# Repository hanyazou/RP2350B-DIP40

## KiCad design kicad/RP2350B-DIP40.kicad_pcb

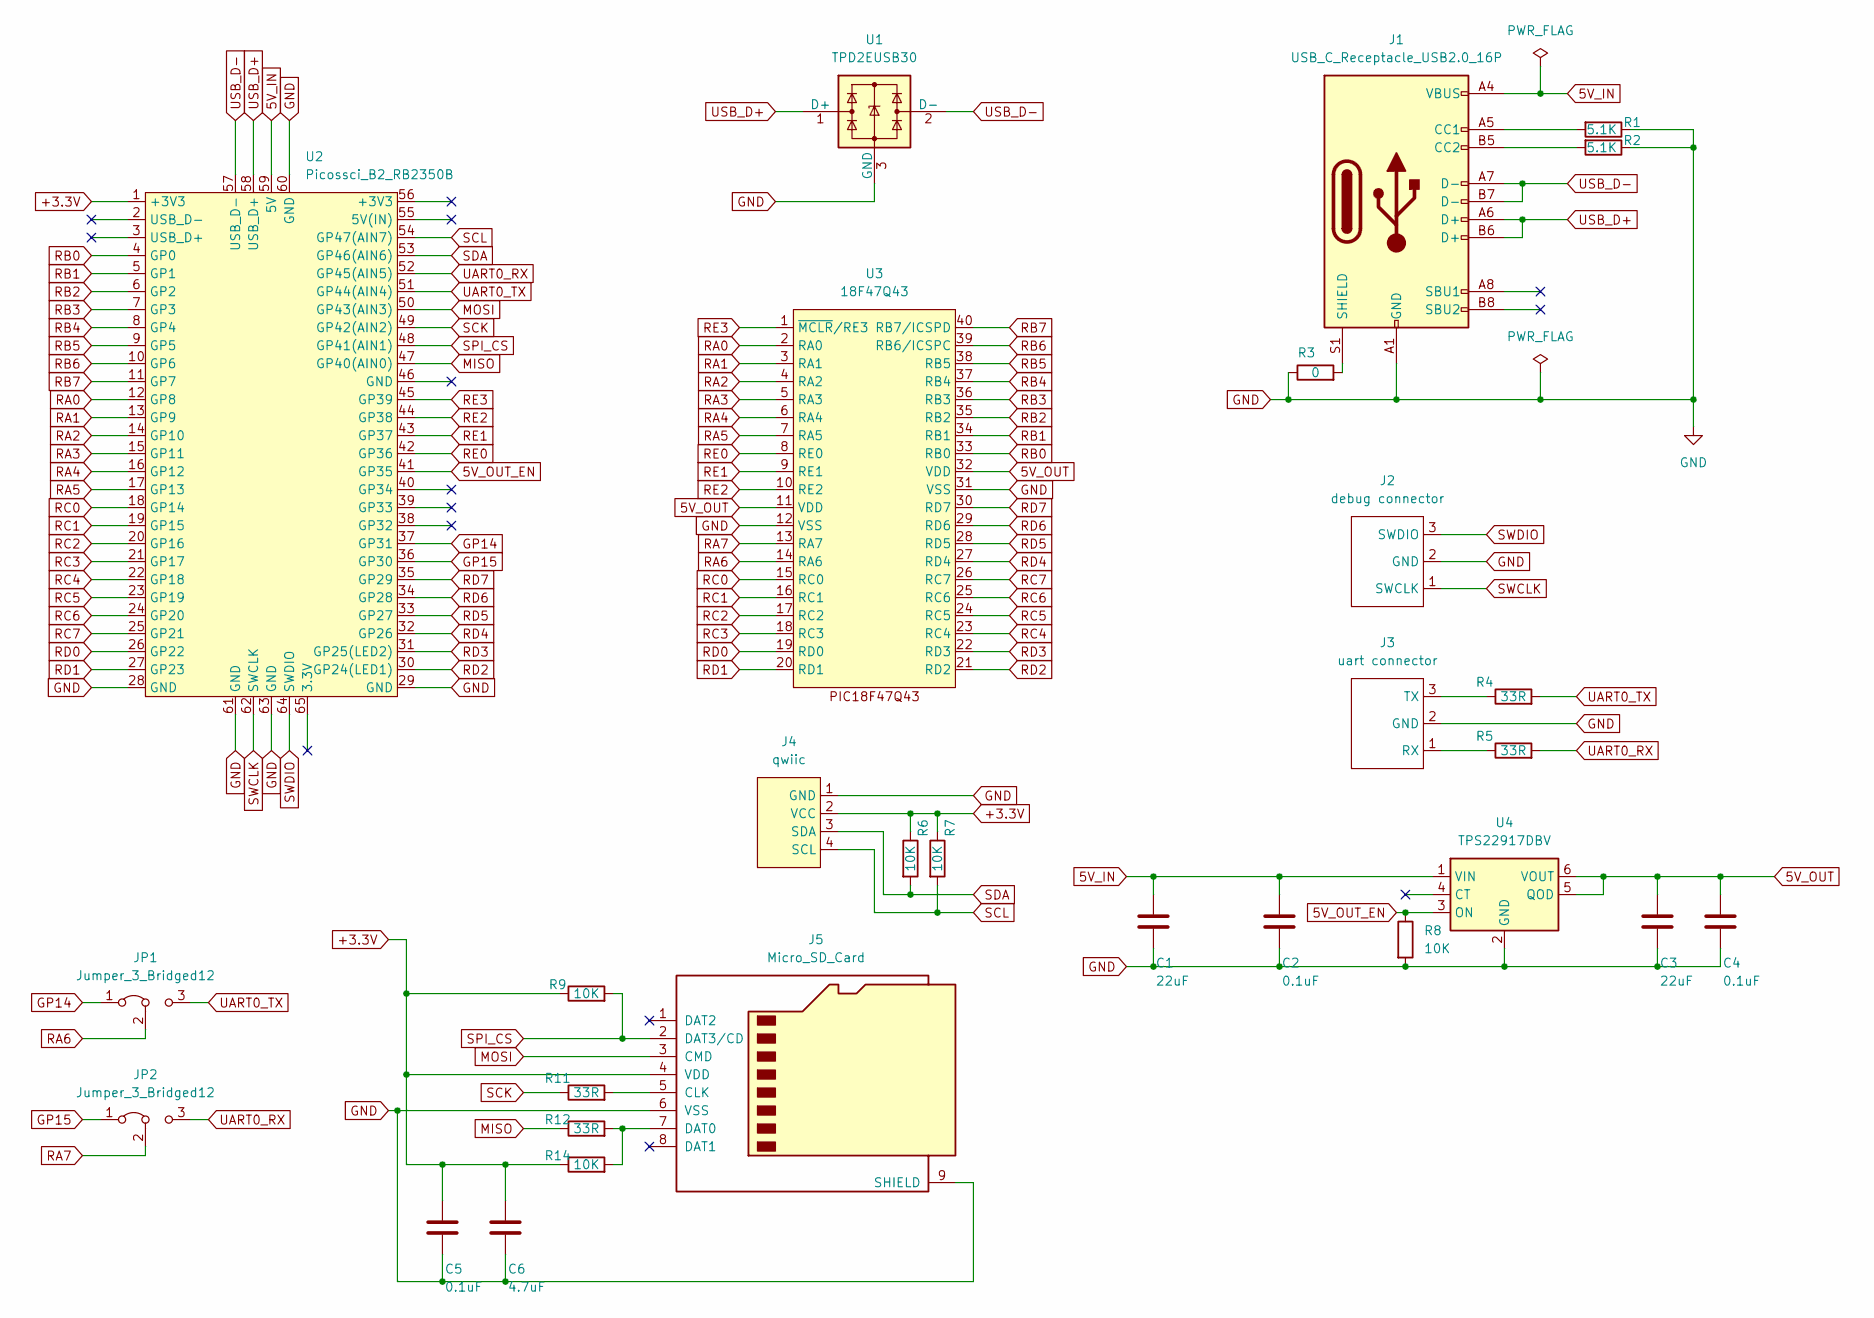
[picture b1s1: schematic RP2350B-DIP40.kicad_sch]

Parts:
C1, C3: 22uF; C_0805_2012Metric_Pad1.18x1.45mm_HandSolder
C2, C4, C5: 0.1uF; C_0603_1608Metric_Pad1.08x0.95mm_HandSolder
C6: 4.7uF; C_0603_1608Metric_Pad1.08x0.95mm_HandSolder
J1: USB_C_Receptacle_USB2.0_16P; USB_C_Receptacle_Neltron_5077CR-16SMC2
J2: debug connector; JST_SH_SM03B-SRSS-TB_1x03-1MP_P1.00mm_Horizontal
J3: uart connector; JST_SH_SM03B-SRSS-TB_1x03-1MP_P1.00mm_Horizontal
J4: qwiic; JST_SH_SM04B-SRSS-TB_1x04-1MP_P1.00mm_Horizontal
J5: Micro_SD_Card; microSD_HC_Hirose_DM3AT-SF-PEJM5
JP1, JP2: Jumper_3_Bridged12; SolderJumper-3_P1.3mm_Bridged12_RoundedPad1.0x1.5mm_NumberL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
R1, R2: 5.1K; R_0603_1608Metric_Pad0.98x0.95mm_HandSolder
R3: 0; R_0603_1608Metric_Pad0.98x0.95mm_HandSolder
R4, R5, R11, R12: 33R; R_0603_1608Metric_Pad0.98x0.95mm_HandSolder
R6, R7, R8, R9, R14: 10K; R_0603_1608Metric_Pad0.98x0.95mm_HandSolder
U1: TPD2EUSB30; Texas_DRT-3
U2: Picossci_B2_RB2350B; Picossci_2B_RP2350B
U3: 18F47Q43; Pin_Header-2x20_SMD
U4: TPS22917DBV; SOT-23-6

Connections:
5V_IN: C1.1, C2.1, J1.A4 (VBUS), J1.A9 (VBUS), J1.B4 (VBUS), J1.B9 (VBUS), U2.59 (5V), U4.1 (VIN)
5V_OUT: C3.1, C4.1, U3.11 (VDD), U3.32 (VDD), U4.5 (QOD), U4.6 (VOUT)
5V_OUT_EN: R8.1, U2.41 (GP35), U4.3 (ON)
+3.3V: C5.1, C6.1, J4.2 (VCC), J5.4 (VDD), R6.1, R7.1, R9.1, R14.1, U2.1 (+3V3)
GND: C1.2, C2.2, C3.2, C4.2, C5.2, C6.2, J1.A1 (GND), J1.A12 (GND), J1.B1 (GND), J1.B12 (GND), J2.2 (GND), J3.2 (GND), J4.1 (GND), J5.6 (VSS), J5.9 (SHIELD), R1.1, R2.1, R3.1, R8.2, U1.3 (GND), U2.28 (GND), U2.29 (GND), U2.60 (GND), U2.61 (GND), U2.63 (GND), U3.12 (VSS), U3.31 (VSS), U4.2 (GND)
GP14: JP1.1 (A), U2.37 (GP31)
GP15: JP2.1 (A), U2.36 (GP30)
MISO: R12.1, U2.47 (GP40(AIN0))
MOSI: J5.3 (CMD), U2.50 (GP43(AIN3))
unnamed: J1.A5 (CC1), R1.2
unnamed: J1.B5 (CC2), R2.2
unnamed: J1.S1 (SHIELD), R3.2
unnamed: J3.1 (RX), R5.1
unnamed: J3.3 (TX), R4.1
unnamed: J5.5 (CLK), R11.2
unnamed: J5.7 (DAT0), R12.2, R14.2
RA0: U2.12 (GP8), U3.2 (RA0)
RA1: U2.13 (GP9), U3.3 (RA1)
RA2: U2.14 (GP10), U3.4 (RA2)
RA3: U2.15 (GP11), U3.5 (RA3)
RA4: U2.16 (GP12), U3.6 (RA4)
RA5: U2.17 (GP13), U3.7 (RA5)
RA6: JP1.2 (C), U3.14 (RA6)
RA7: JP2.2 (C), U3.13 (RA7)
RB0: U2.4 (GP0), U3.33 (RB0)
RB1: U2.5 (GP1), U3.34 (RB1)
RB2: U2.6 (GP2), U3.35 (RB2)
RB3: U2.7 (GP3), U3.36 (RB3)
RB4: U2.8 (GP4), U3.37 (RB4)
RB5: U2.9 (GP5), U3.38 (RB5)
RB6: U2.10 (GP6), U3.39 (RB6/ICSPC)
RB7: U2.11 (GP7), U3.40 (RB7/ICSPD)
RC0: U2.18 (GP14), U3.15 (RC0)
RC1: U2.19 (GP15), U3.16 (RC1)
RC2: U2.20 (GP16), U3.17 (RC2)
RC3: U2.21 (GP17), U3.18 (RC3)
RC4: U2.22 (GP18), U3.23 (RC4)
RC5: U2.23 (GP19), U3.24 (RC5)
RC6: U2.24 (GP20), U3.25 (RC6)
RC7: U2.25 (GP21), U3.26 (RC7)
RD0: U2.26 (GP22), U3.19 (RD0)
RD1: U2.27 (GP23), U3.20 (RD1)
RD2: U2.30 (GP24(LED1)), U3.21 (RD2)
RD3: U2.31 (GP25(LED2)), U3.22 (RD3)
RD4: U2.32 (GP26), U3.27 (RD4)
RD5: U2.33 (GP27), U3.28 (RD5)
RD6: U2.34 (GP28), U3.29 (RD6)
RD7: U2.35 (GP29), U3.30 (RD7)
RE0: U2.42 (GP36), U3.8 (RE0)
RE1: U2.43 (GP37), U3.9 (RE1)
RE2: U2.44 (GP38), U3.10 (RE2)
RE3: U2.45 (GP39), U3.1 (~MCLR/RE3)
SCK: R11.1, U2.49 (GP42(AIN2))
SCL: J4.4 (SCL), R7.2, U2.54 (GP47(AIN7))
SDA: J4.3 (SDA), R6.2, U2.53 (GP46(AIN6))
SPI_CS: J5.2 (DAT3/CD), R9.2, U2.48 (GP41(AIN1))
SWCLK: J2.1 (SWCLK), U2.62 (SWCLK)
SWDIO: J2.3 (SWDIO), U2.64 (SWDIO)
UART0_RX: JP2.3 (B), R5.2, U2.52 (GP45(AIN5))
UART0_TX: JP1.3 (B), R4.2, U2.51 (GP44(AIN4))
USB_D+: J1.A6 (D+), J1.B6 (D+), U1.1 (D+), U2.58 (USB_D+)
USB_D-: J1.A7 (D-), J1.B7 (D-), U1.2 (D-), U2.57 (USB_D-)

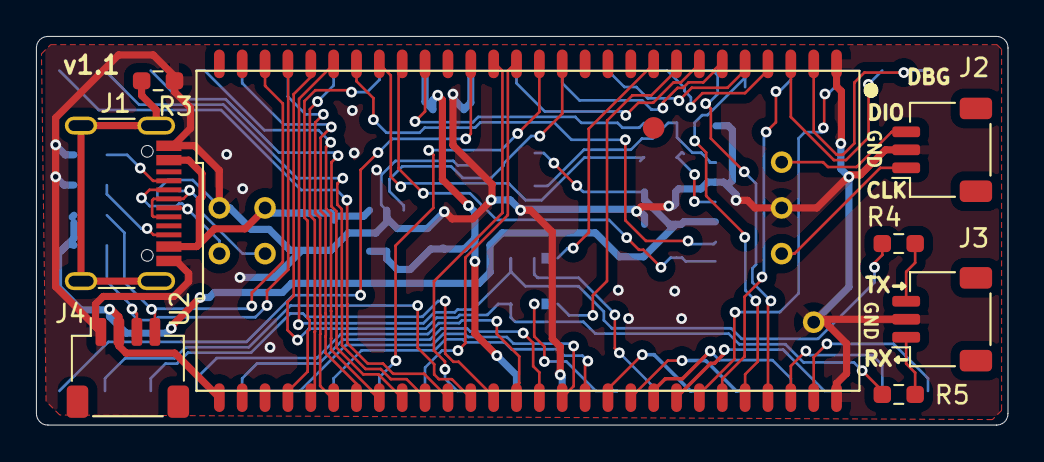
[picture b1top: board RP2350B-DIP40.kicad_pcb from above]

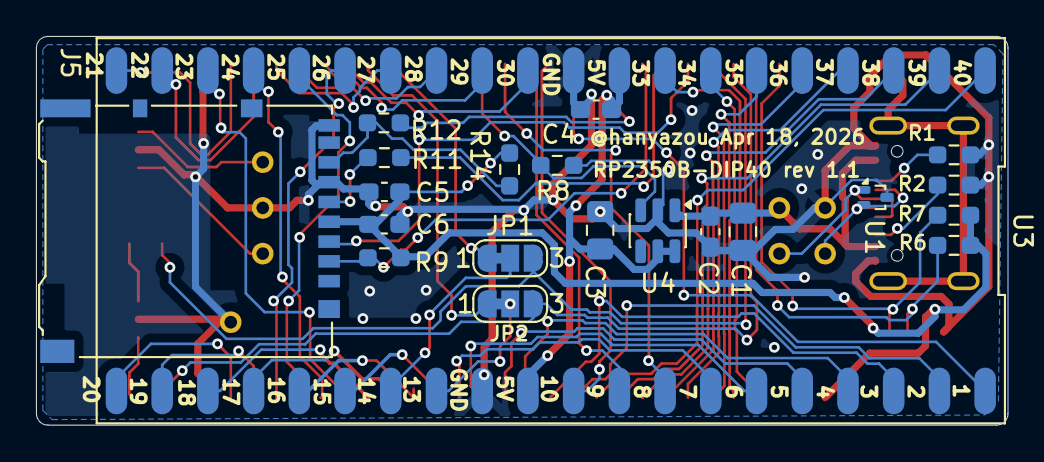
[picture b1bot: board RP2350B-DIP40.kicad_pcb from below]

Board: 2 copper layers, 54.0 x 21.6 mm, 29 parts (20 on the bottom side), 62 nets.

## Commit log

2026-03-08 Add PCB design RP2350B-DIP40-rev0.8
2026-03-08 Add schematic.pdf
2026-03-21 Add piko SDK submodule
2026-03-22 Add RP2350B-DIP40-rev0.91.zip
2026-03-22 Add test programs
2026-03-22 Add PCB design RP2350B-DIP40-rev1.0
2026-04-12 Fix test protrams
2026-04-18 Add PCB design RP2350B-DIP40-rev1.1
2026-05-02 Fix pins test for PCB rev1.1
